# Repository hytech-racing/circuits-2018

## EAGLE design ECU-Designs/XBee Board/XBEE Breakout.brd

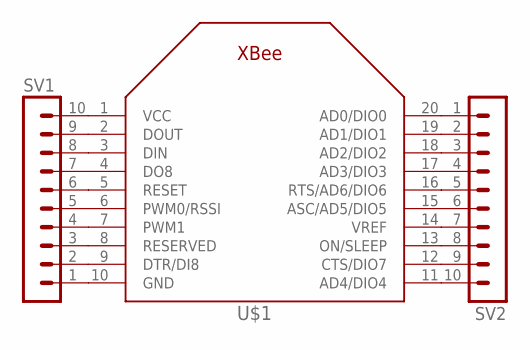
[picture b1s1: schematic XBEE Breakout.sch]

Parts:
SV1, SV2: MA10-1
U$1: XBEE

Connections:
GND: SV1.1, U$1.10 (GND)
unnamed: SV1.2, U$1.9 (DTR/DI8)
unnamed: SV1.3, U$1.8 (RESERVED)
unnamed: SV1.4, U$1.7 (PWM1)
unnamed: SV1.5, U$1.6 (PWM0/RSSI)
unnamed: SV1.6, U$1.5 (RESET)
unnamed: SV1.7, U$1.4 (DO8)
unnamed: SV1.8, U$1.3 (DIN)
unnamed: SV1.9, U$1.2 (DOUT)
unnamed: SV2.1, U$1.20 (AD0/DIO0)
unnamed: SV2.2, U$1.19 (AD1/DIO1)
unnamed: SV2.3, U$1.18 (AD2/DIO2)
unnamed: SV2.4, U$1.17 (AD3/DIO3)
unnamed: SV2.5, U$1.16 (RTS/AD6/DIO6)
unnamed: SV2.6, U$1.15 (ASC/AD5/DIO5)
unnamed: SV2.7, U$1.14 (VREF)
unnamed: SV2.8, U$1.13 (ON/SLEEP)
unnamed: SV2.9, U$1.12 (CTS/DIO7)
unnamed: SV2.10, U$1.11 (AD4/DIO4)
VCC: SV1.10, U$1.1 (VCC)

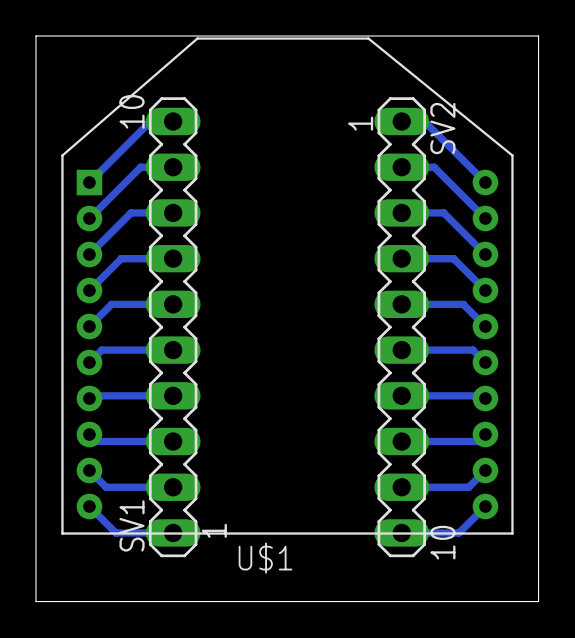
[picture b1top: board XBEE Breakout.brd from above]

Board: 2 copper layers, 27.9 x 31.4 mm, 3 parts (0 on the bottom side), 20 nets.
